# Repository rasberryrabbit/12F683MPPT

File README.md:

# 12F683MPPT
Simple MPPT with 12F683  
  
Another porting of MPPT. Test ok. Switching frequency : 10kHz.  
It has no switching noise.  
  
BUK9508-55A for alternative FET. 
  
TLC272 OPAMP works better. MCP602 is better for low temperature condition.  
  
(Note) Sometimes MPPT stalls no output. It caused by low FET bootstrap voltage.  
It's very rare condition. It may fixed by R9 change.

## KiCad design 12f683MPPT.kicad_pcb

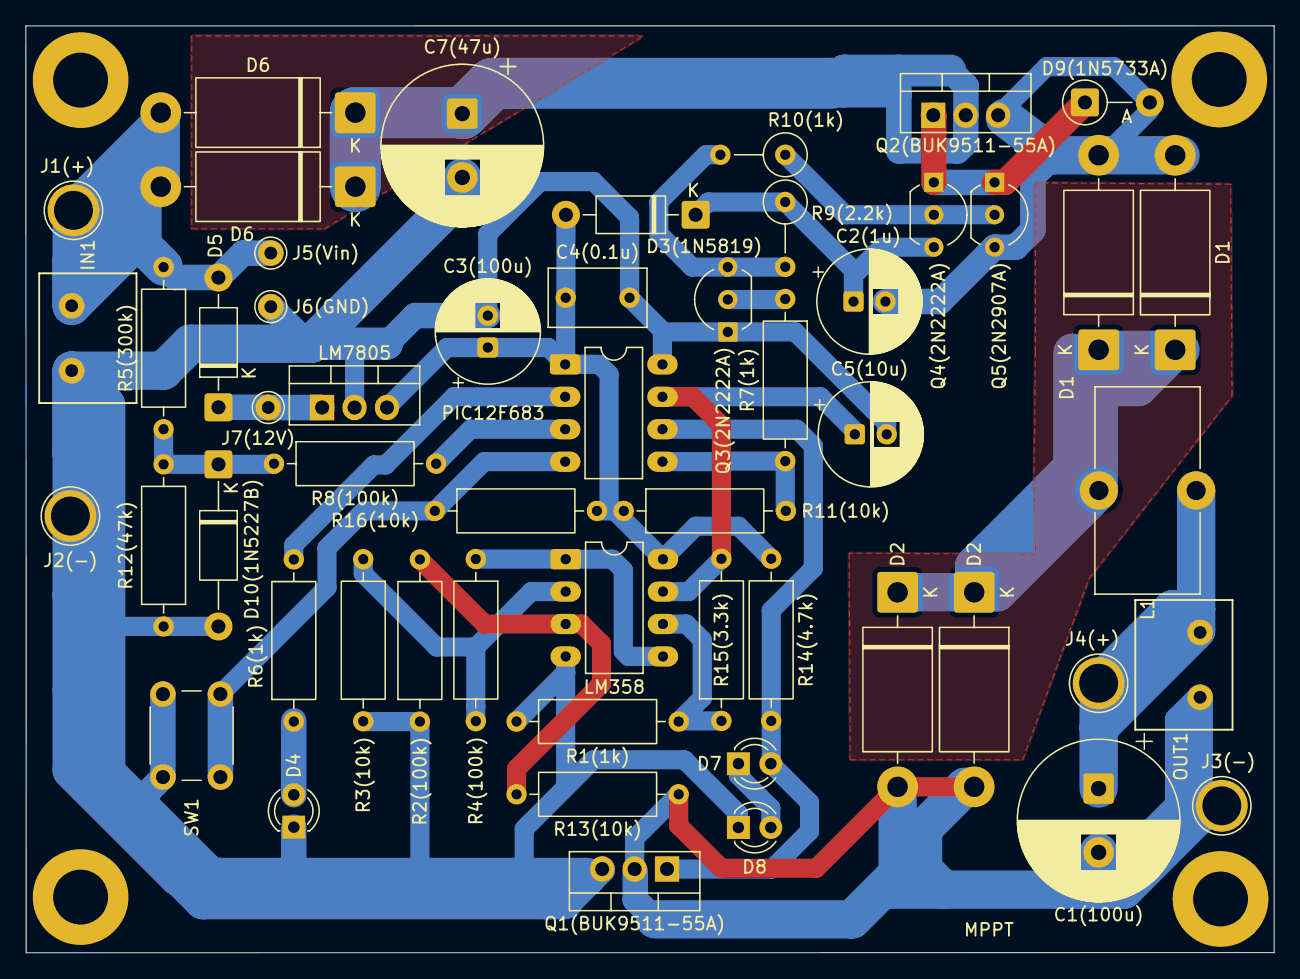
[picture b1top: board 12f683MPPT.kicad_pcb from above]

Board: 2 copper layers, 97.8 x 72.6 mm, 54 parts (0 on the bottom side), 27 nets.

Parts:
C1(100u): 100u; CP_Radial_D12.5mm_P5.00mm
C2(1u): 4.7u 50v; CP_Radial_D8.0mm_P2.50mm
C3(100u): 100u; CP_Radial_D8.0mm_P2.50mm
C4(0.1u): 0.1u; C_Disc_D7.5mm_W4.4mm_P5.00mm
C5(10u): 10u; CP_Radial_D8.0mm_P2.50mm
C7(47u): 47u; CP_Radial_D12.5mm_P5.00mm
D1, D1#2, D2, D2#2, D6, D6#2: 1N5822A; D_DO-201AD_P15.24mm_Horizontal
D3(1N5819): 1N5819; D_DO-41_SOD81_P10.16mm_Horizontal
D4, D7, D8: LED; LED_D3.0mm
D5: 1N4007; D_DO-41_SOD81_P10.16mm_Horizontal
D9(1N5733A): 1N5733A 5.1V; D_DO-41_SOD81_P5.08mm_Vertical_AnodeUp
D10(1N5227B): 1N5227B; D_DO-41_SOD81_P12.70mm_Horizontal
IN1: Conn_01x02_Male; Connector_SCREW_2PIN
J1(+), J2(-), J3(-), J4(+): Conn_01x01_Male; 1pin
J5(Vin): Vin; Pin_D1.0mm_L10.0mm
J6(GND): GND; Pin_D1.0mm_L10.0mm
J7(12V): 12V; Pin_D1.0mm_L10.0mm
L1: 330uH 3A; L_Toroid_Vertical_L16.0mm_W8.0mm_P7.62mm
LM358: LM358; DIP-8_W7.62mm_LongPads
LM7805: LM7805_TO220; TO-220-3_Vertical
OUT1: Conn_01x02_Male; Connector_SCREW_2PIN
PIC12F683: PIC12F683-IP; DIP-8_W7.62mm_LongPads
Q1(BUK9511-55A), Q2(BUK9511-55A): BUK9511-55A127; TO-220-3_Vertical
Q3(2N2222A), Q4(2N2222A): 2N2222A; TO-92_Inline_Wide
Q5(2N2907A): 2N2907A; TO-92_Inline_Wide
R1(1k), R6(1k), R7(1k): 1k; R_Axial_DIN0309_L9.0mm_D3.2mm_P12.70mm_Horizontal
R2(100k), R4(100k), R8(100k): 100k; R_Axial_DIN0309_L9.0mm_D3.2mm_P12.70mm_Horizontal
R3(10k), R11(10k), R13(10k), R16(10k): 10k; R_Axial_DIN0309_L9.0mm_D3.2mm_P12.70mm_Horizontal
R5(300k): 300k; R_Axial_DIN0309_L9.0mm_D3.2mm_P12.70mm_Horizontal
R9(2.2k): 2.2k; R_Axial_DIN0309_L9.0mm_D3.2mm_P5.08mm_Vertical
R10(1k): 1k; R_Axial_DIN0309_L9.0mm_D3.2mm_P5.08mm_Vertical
R12(47k): 47k; R_Axial_DIN0309_L9.0mm_D3.2mm_P12.70mm_Horizontal
R14(4.7k): 4.7k; R_Axial_DIN0309_L9.0mm_D3.2mm_P12.70mm_Horizontal
R15(3.3k): 3.3k; R_Axial_DIN0309_L9.0mm_D3.2mm_P12.70mm_Horizontal
SW1: SW_Push; SW_PUSH_6mm_H7.3mm

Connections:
+24V: D5.2 (A), D6.2 (A), D6#2.2 (A), IN1.1, J1(+).1, J5(Vin).1, R5(300k).1
/3.6v: D7.2 (A), PIC12F683.6 (GP1), Q1(BUK9511-55A).1 (G), R14(4.7k).2
/BootStrap: C2(1u).1, D3(1N5819).1 (K), Q4(2N2222A).3 (C), R9(2.2k).1
/PV-Current: C5(10u).1, LM358.7, PIC12F683.7 (GP0), R15(3.3k).2
/PV-Voltage: PIC12F683.3 (GP4), R8(100k).2
GNDPWR: C3(100u).2, C4(0.1u).2, C5(10u).2, C7(47u).2, D4.1 (K), D8.1 (K), D10(1N5227B).2 (A), IN1.2, J2(-).1, J6(GND).1, LM358.4 (V-), LM7805.2 (GND), PIC12F683.8 (VSS), Q1(BUK9511-55A).3 (S), Q3(2N2222A).1 (E), R1(1k).1, R2(100k).1, R3(10k).2, R12(47k).2, SW1.1
unnamed: C2(1u).2, D1.2 (A), D1#2.2 (A), D9(1N5733A).2 (A), Q2(BUK9511-55A).3 (S), Q5(2N2907A).3 (C)
unnamed: D1.1 (K), D1#2.1 (K), D2.1 (K), D2#2.1 (K), L1.1
unnamed: C3(100u).1, C4(0.1u).1, D3(1N5819).2 (A), LM358.8 (V+), LM7805.3 (VO), PIC12F683.1 (VDD), R11(10k).1, R14(4.7k).1, R16(10k).2
unnamed: D4.2 (A), R6(1k).1
unnamed: D5.1 (K), J7(12V).1, LM7805.1 (VI)
unnamed: C7(47u).1, D6.1 (K), D6#2.1 (K), Q2(BUK9511-55A).2 (D)
unnamed: D7.1 (K), D8.2 (A)
unnamed: D9(1N5733A).1 (K), Q2(BUK9511-55A).1 (G), Q4(2N2222A).1 (E), Q5(2N2907A).1 (E)
unnamed: D10(1N5227B).1 (K), R5(300k).2, R8(100k).1, R12(47k).1
unnamed: Q3(2N2222A).2 (B), R7(1k).1
unnamed: Q3(2N2222A).3 (C), R9(2.2k).2, R10(1k).2
unnamed: Q4(2N2222A).2 (B), Q5(2N2907A).2 (B), R10(1k).1
unnamed: PIC12F683.5 (GP2), R7(1k).2, R11(10k).2
unnamed: PIC12F683.4 (GP3), R16(10k).1, SW1.2
unnamed: PIC12F683.2 (GP5), R6(1k).2
unnamed: LM358.3 (+), R2(100k).2, R13(10k).2
unnamed: LM358.2 (-), R3(10k).1, R4(100k).2
unnamed: LM358.1, LM358.5 (+), R4(100k).1
unnamed: LM358.6 (-), R1(1k).2, R15(3.3k).1
PRI_HI: C1(100u).1, J4(+).1, L1.2, OUT1.2
PRI_LO: C1(100u).2, D2.2 (A), D2#2.2 (A), J3(-).1, OUT1.1, Q1(BUK9511-55A).2 (D), R13(10k).1

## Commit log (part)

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2019-05-20 First. Not tested yet.
2019-05-20 update PCB.
2019-05-20 Fix ANSEL.
2019-06-03 Test ok. Update comments.
2019-06-03 update.
2019-06-03 update comment.
2019-06-03 Fix connector foot print.
2019-06-04 Fix OSC and timer1 prescaler.
2019-06-09 Remove low voltage protection code and test.
2019-07-16 lower checking interval.
2019-07-21 back to 30ms.
2020-05-28 Mount Hole size to 3mm. It's lower value for normal mounting.
2020-05-28 Fix drl file.
2020-05-28 Remove invalid drl file.
2020-09-30 Change configuration BOREN.
2021-04-28 Enable BOR
2021-04-30 Add zener diode for FET protection.
2021-05-02 Update PDF
2021-05-07 R9 -> 2.2k
2021-05-28 Mininum PWM limit to 15.
2021-05-30 Set low PWM to 12.
2021-07-09 C2 -> 4.7uF
2021-07-29 Try to fix low bootstrap voltage.
2021-07-30 Revert PWM_MIN.
2021-07-30 Revert and change Diode.
2021-08-01 Fix power comparison.
2021-08-02 Revert.
2022-01-14 Compiled by mikro Pascal 7.6.0
2025-11-25 Fix circuit. R1 -> 1k ohm.
2025-11-25 Add new KiCad files.
2025-11-25 Remove old circuit.
2025-11-25 Add current measurement hint.
2025-11-26 Fix PWM bug.
2025-11-26 More fix on PWM.
2025-11-27 Set PWM start duty cycle to 30%.
2025-11-27 Try limiting PWM at low current.
2025-11-27 Update OP-AMP selection hint.
2025-11-28 Update PCB options.
2025-11-28 Remove old verison files.
2025-12-01 Remove low current counting. It's useless.
2025-12-02 Remove files.
2025-12-02 Update PCB files.
2025-12-02 Update circuit.
2025-12-02 Add zener for input voltage limiting.
2025-12-02 More PCB files changes.
2025-12-03 Remove unused code. No functional changes.
2025-12-14 Add hint for D3 alternative.
2025-12-28 Add GNU GPL v3 license file
    Added the GNU General Public License version 3 to the project.
2026-03-06 Reduce checking interval.
2026-03-10 Increase checking interval.
2026-03-11 Increase a little checking interval. Not much changes output power. most stable value is 18ms.
2026-03-18 Revert checking interval to 18ms.
